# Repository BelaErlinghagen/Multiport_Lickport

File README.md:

# The Multiport Setup

**A behavioral setup for mice with 16 reward ports, multiple light/sound cues and real time pose estimation.**

<p align="center">
  <em>
    <b>Figure 1: The Multiport Setup.</b>
    <b>A)</b> Complete view of the Multiport Setup.
    <b>B)</b> Testing adjustments to the setup to show that the capacitive sensor of the Lick-O-Tron detects mouse licks.
    A Basler daA1440 was used to record the lickport. The mouse was given condensed milk (white droplet in C) manually through the shown tube.
    <b>C)</b> <i>Top:</i> Timeline over the entire session, with sensor activations marked as blue bars.
    <i>Bottom:</i> Zoom into one lick detection.
  </em>
</p>

---

## Table of Contents

- [Components of the Multiport Setup](#components-of-the-multiport-setup)
  - [Arena](#arena)
  - [Lick-O-Tron and PORTMASTER](#lick-o-tron-and-portmaster)
  - [Computer](#computer)
  - [Projector](#projector)
  - [Camera](#camera)
  - [Screens](#screens)
- [The Lick-O-Tron Lickport](#the-lick-o-tron-lickport)
  - [Design](#design)
  - [Assembly](#assembly)
    - [Parts](#parts)
    - [Step 1: Soldering](#step-1-soldering)
    - [Step 2: Uploading the code and testing the sensor](#step-2-uploading-the-code-and-testing-the-sensor)
    - [Step 3: Preparing the cannula](#step-3-preparing-the-cannula)
    - [Step 4: Assembly](#step-4-assembly)
    - [Step 5: Add the pump](#step-5-add-the-pump)
  - [Usage](#usage)
- [The PORTMASTER](#the-portmaster)
  - [Design](#design-1)
  - [Assembly](#assembly-1)
    - [Parts](#parts-1)
    - [Step 1: Solder pins and connector pieces to the PCB](#step-1-solder-pins-and-connector-pieces-to-the-pcb)
    - [Step 2: Wiring](#step-2-wiring)
  - [Usage](#usage-1)
- [Credit](#credit)

---

## Components of the Multiport Setup

### Arena

The arena is built from 16 [red acrylic wall panels](ArenaFiles/ArenaWall.stp), held together by 16 [connector pieces](ArenaFiles/AnglePiece.stp). This circular assembly stands on a sheet of acrylic that has been roughened on one side, which makes it more comfortable for the mice to walk on and prevents light projected onto the arena floor from being reflected.

In addition to the circular Multiport arena, two inlets were created to form a Y-Maze.

### Lick-O-Tron and PORTMASTER

The **Lick-O-Tron** is a self-built lickport module consisting of a capacitive sensor, an LED and a MOSFET relay to trigger a pump or valve.

The **PORTMASTER** is a hub that connects all Lick-O-Trons to the master Arduinos and delivers power to the pumps.

Both components are documented in detail below: see [The Lick-O-Tron Lickport](#the-lick-o-tron-lickport) and [The PORTMASTER](#the-portmaster).

### Computer

The computer used in this build was a Lenovo Thinkstation with the following specifications:

| Component | Specification |
| :--- | :--- |
| CPU | Intel(R) Core(TM) i7-14700K |
| GPU | Nvidia GeForce RTX 4060 |
| OS  | Ubuntu 24.04 |

To run live inference with DeepLabCut, CUDA was installed alongside the necessary Nvidia GPU drivers. Pixi was used to manage the Python environment of the software; the `.lock` and `.toml` files can be found in this repository.

### Projector

A BenQ Cinema Master Projector was mounted approximately 200 cm above the arena floor.

### Camera

A Basler daA3840-45uc camera with an Evetar lens (E3417A F2.4 f2.5mm 1/1.8") was mounted 40 cm below the arena floor.

### Screens

In the Y-Maze configuration, two Adafruit screens (5" 800x480 HDMI Backpack) were used to display patterns for the mice. The screens were mounted on [custom holders](ArenaFiles/YMaze_ScreenHolder.stp) that fit the Y-Maze configuration, and were connected directly to the computer via HDMI.

---

# Documentation for the Lick-O-Tron and the PORTMASTER

The Lick-O-Tron lickport and the PORTMASTER connectivity board are the two major components that act together in the automated Multiport system. Their design, assembly and usage are explained in detail below. The files needed to recreate the two modules can be found in their respective folders.

## The Lick-O-Tron Lickport

The idea behind the Lick-O-Tron was to create a lickport for behavioral mouse experiments that can:

1. Register lick events via a capacitive sensor.
2. Connect to up to two peristaltic pumps, which can independently eject precise volumes of liquid.
3. Allow flexible control of an LED located next to the needle.

### Design

The Lick-O-Tron contains three submodules: one Arduino proMicro and two MOSFET relay modules. The Arduino proMicro, as well as the power outlets of the MOSFET relay modules, receive power via the main connector (8-pin plug).

The Arduino's job is to register licks via a capacitive sensor — a cannula connected to the single pin at the bottom of the Lick-O-Tron. This is achieved with the code found [here](Lick-O-Tron/LickportArduinoCode.ino). The Arduino then transmits binary data about lick events to the Arduino Megas housed on the PORTMASTER.

The MOSFET modules are activated by the master Arduinos on the PORTMASTER and can trigger peristaltic pumps (or valves, etc.). The idea is that lick information is received by the master Arduinos, which then activate the pumps at set timepoints and with set PWM, depending on the needs of the experimenter. This allows for very flexible control of liquid dispensation. The Lick-O-Tron further connects the master Arduinos to an LED, which can be controlled independently.

<p align="center">
  <em><b>Figure 2:</b> 3D CAD model renderings for the Lick-O-Tron (left: front, middle: back, right: case). Note that the Pin Connectors are not depicted correctly in this Figure: The 8 Pin Header is straight and supposed to be soldered onto the other side of the PCB and the two angular 2 Pin Headers are also depicted on the wrong side of the PCB.</em>
</p>

### Assembly

#### Parts

| Item | Quantity | Manufactured by | EAN |
| :--- | ---: | :--- | ---: |
| Joy It proMicro | 1 | Joy It | 4250236822907 |
| MOSFET Relay Module | 2 | for example GERUI | 0744243396666 |
| Mini Peristaltic Pump | 1 (up to 2) | Whadda | 5410329730017 |
| Lick-O-Tron PCB | 1 | Eurocircuits | None: see folder in repo |
| Lick-O-Tron Case Parts | 1 each | 3D printed | None: see folder in repo |
| LED (white) | 1 | TRU Components | 2050004902785 |
| 10 MOhm Resistor (R1) | 1 | TRU Components | 2050004926057 |
| 470 Ohm Resistor (R2) | 1 | TRU Components | 4016139313023 |
| M3 Screws | 4 | Toolcraft | 4064161107578 |
| M3 Nuts | 4 | SWG Hox | 4053056028951 |
| Sterican Cannula | 2 | Roth | - |

#### Step 1: Soldering

With the PCB, the proMicro, the LED, the resistors, some pins and the relay modules at hand, the first step is to solder all of these components onto the PCB. By the end, the PCB should look similar to what is shown in Figure 2.

#### Step 2: Uploading the code and testing the sensor

Upload the Lick-O-Tron [code](Lick-O-Tron/LickportArduinoCode.ino) from this repository to the Joy It proMicro using the Arduino IDE. Then use the serial monitor to test whether touching the sensor pin registers something.

#### Step 3: Preparing the cannula

<p align="center">
  <em><b>Figure 3:</b> Example cannula assembly.</em>
</p>

To electrically connect the cannula to the sensor pin, a wire was wrapped around the cannula and clamped to it, and a second wire was then soldered onto the first one. This second wire was soldered to a pin connector piece, which connects to the sensor pin.

#### Step 4: Assembly

Once all these pieces are ready, the Lick-O-Tron can be assembled. In the Multiport build previewed here, the PCB was simply placed into the 3D-printed chamber and everything was screwed together directly onto the arena, where the spout frame had already been fixed into the acrylic sheets.

#### Step 5: Add the pump

To add the pump, solder two wires to the solder flags and their other ends to a pin connector. To rebuild the setup shown here exactly, 3D print the pump holder pieces and attach the pump as shown in Figure 4.

### Usage

<p align="center">
  <em><b>Figure 4:</b> All pieces together.</em>
</p>

The Lick-O-Tron is connected to the PORTMASTER via an 8-band ribbon cable. One PORTMASTER can control up to 16 Lick-O-Trons.

---

## The PORTMASTER

<p align="center">
  <em><b>Figure 5:</b> The PORTMASTER rack, lid opened.</em>
</p>

### Design

The PORTMASTER is designed to:

- power up to five 6 V pumps comfortably (more are possible);
- provide an easily accessible interface between the Arduinos and the computer, BNCs and power supply.

### Assembly

#### Parts

| Item | Quantity | Manufactured by | EAN |
| :--- | ---: | :--- | ---: |
| Arduino Mega 2560 Rev3 | 2 | Arduino | 7630049200067 |
| 8-band ribbon cable | - | - | - |
| 8-Way IDC Connector Female for Cable, 1 Row | 32 | Wurth Elektronik | 661008151923 (Mf. part #) |
| PORTMASTER PCB | 1 | Eurocircuits | None: see folder in repo |
| RSP-100-5 SMPSU 5V DC 20A 100W | 1 | MEAN WELL | 4711287435657 |

> **Note:** The remaining parts visible in Figure 5 have been left out on purpose, as they are specific to the space in which the Multiport Setup — and especially the PORTMASTER — was housed.

#### Step 1: Solder pins and connector pieces to the PCB

To connect the two Arduino Megas to the PCB, first solder the pins and the connector pieces for the power supply and the BNCs onto the PCB.

#### Step 2: Wiring

Once the Arduinos are in place, all that is left to do is the wiring. The 16 Lick-O-Trons are connected using an 8-band ribbon cable together with two 8-way IDC connectors, one going on the Lick-O-Tron and one on the PORTMASTER. Then the power supply needs to be connected to mains power and to the PCB. In the build showcased here, male BNC plugs were also connected to the PCB.

> **Safety:** Make sure to properly ground the casing of the PORTMASTER.

### Usage

The PORTMASTER can be connected to a computer via two USB-B to USB-A cables. It can then be used with the [custom software](Multiport_Code) in this repository.

---

## Credit

The Lick-O-Tron and the PORTMASTER were conceptualized and designed by Bela Erlinghagen, with extensive support from [Trace Robbins](https://github.com/R-Trace) and [Ben Escribano](https://github.com/BenjaminEscribano) of the iBehave CADRE ([website](https://ibehave.nrw/ibots-platform/cadre/), [GitHub](https://github.com/iBehave-CADRE)).

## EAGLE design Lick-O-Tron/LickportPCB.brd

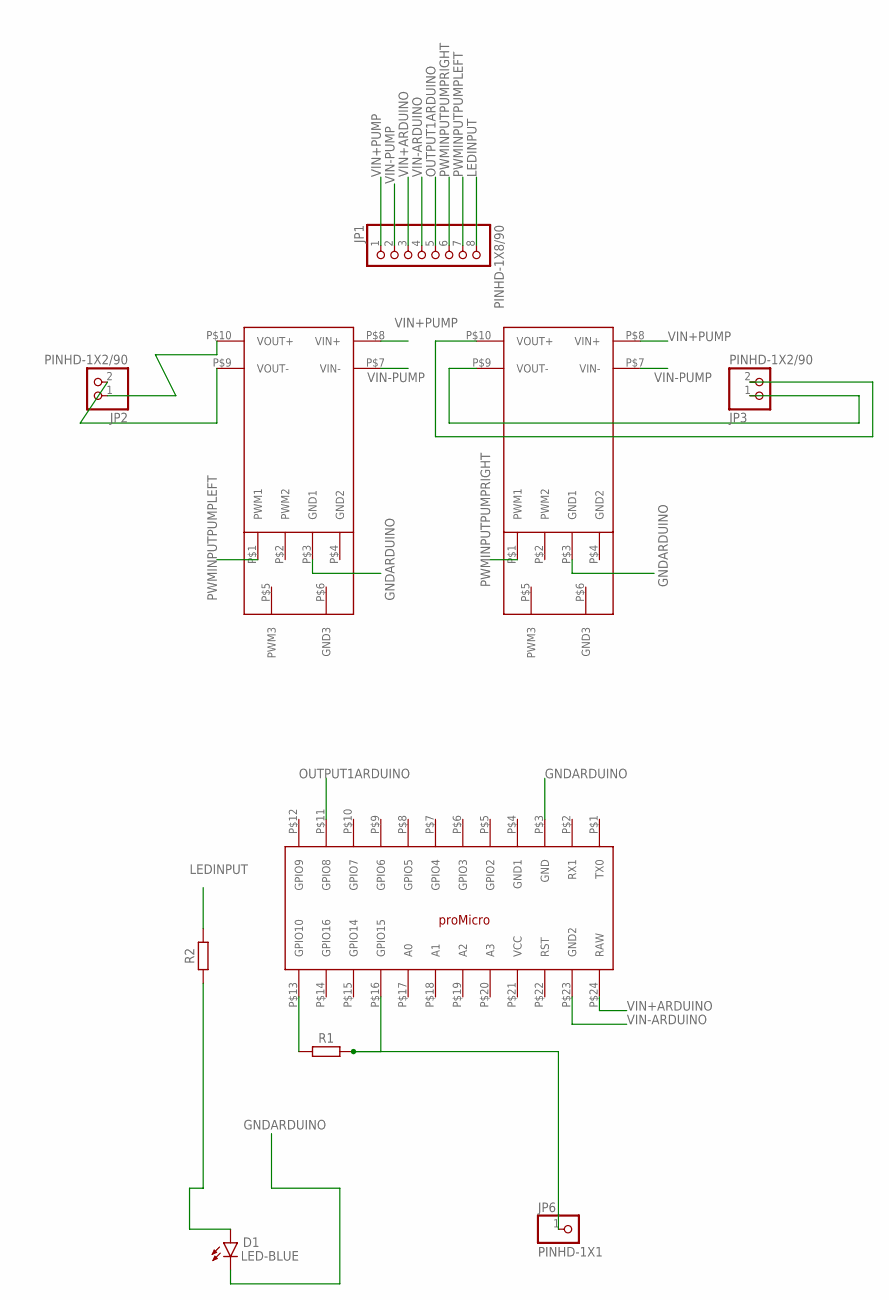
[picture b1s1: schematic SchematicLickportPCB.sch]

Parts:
D1: LED-BLUE; LEDRD254W60D565H860B_B
JP1: PINHD-1X8/90; 1X08/90
JP2, JP3: PINHD-1X2/90; 1X02/90
JP6: PINHD-1X1; 1X01
R1, R2: RESISTOR_AXIAL-11.7MM-PITCH; RESAD1176W63L850D250B
U$1, U$2: MOSFET_MODULE
U$3: JOY_IT_PRO_MICRO

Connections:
GNDARDUINO: D1.C, U$1.P$3 (GND1), U$2.P$3 (GND1), U$3.P$3 (GND)
LEDINPUT: JP1.8, R2.2
unnamed: JP2.1, U$1.P$10 (VOUT+)
unnamed: JP2.2, U$1.P$9 (VOUT-)
unnamed: JP3.2, U$2.P$10 (VOUT+)
unnamed: JP3.1, U$2.P$9 (VOUT-)
unnamed: D1.A, R2.1
unnamed: R1.1, U$3.P$13 (GPIO10)
unnamed: JP6.1, R1.2, U$3.P$16 (GPIO15)
OUTPUT1ARDUINO: JP1.5, U$3.P$11 (GPIO8)
PWMINPUTPUMPLEFT: JP1.7, U$1.P$1 (PWM1)
PWMINPUTPUMPRIGHT: JP1.6, U$2.P$1 (PWM1)
VIN+ARDUINO: JP1.3, U$3.P$24 (RAW)
VIN+PUMP: JP1.1, U$1.P$8 (VIN+), U$2.P$8 (VIN+)
VIN-ARDUINO: JP1.4, U$3.P$23 (GND2)
VIN-PUMP: JP1.2, U$1.P$7 (VIN-), U$2.P$7 (VIN-)

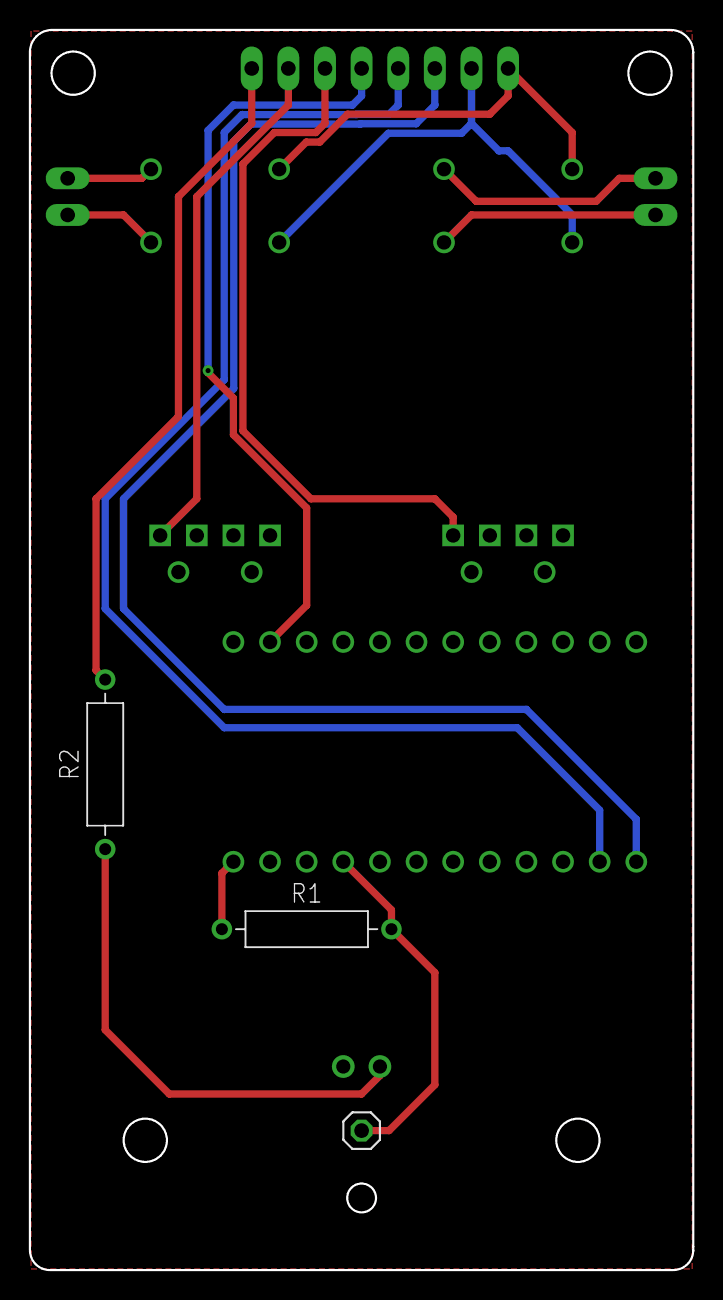
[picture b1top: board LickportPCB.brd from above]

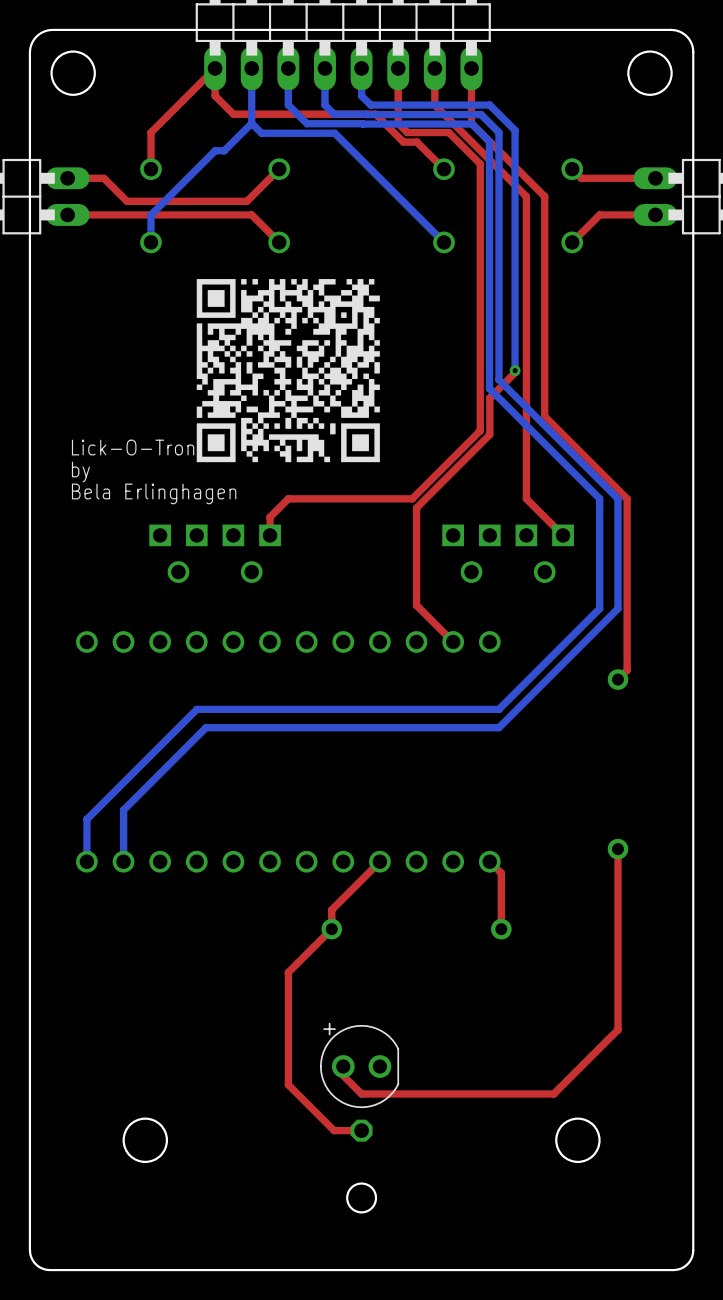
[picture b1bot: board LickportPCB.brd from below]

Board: 2 copper layers, 46.0 x 86.0 mm, 10 parts (4 on the bottom side), 16 nets.

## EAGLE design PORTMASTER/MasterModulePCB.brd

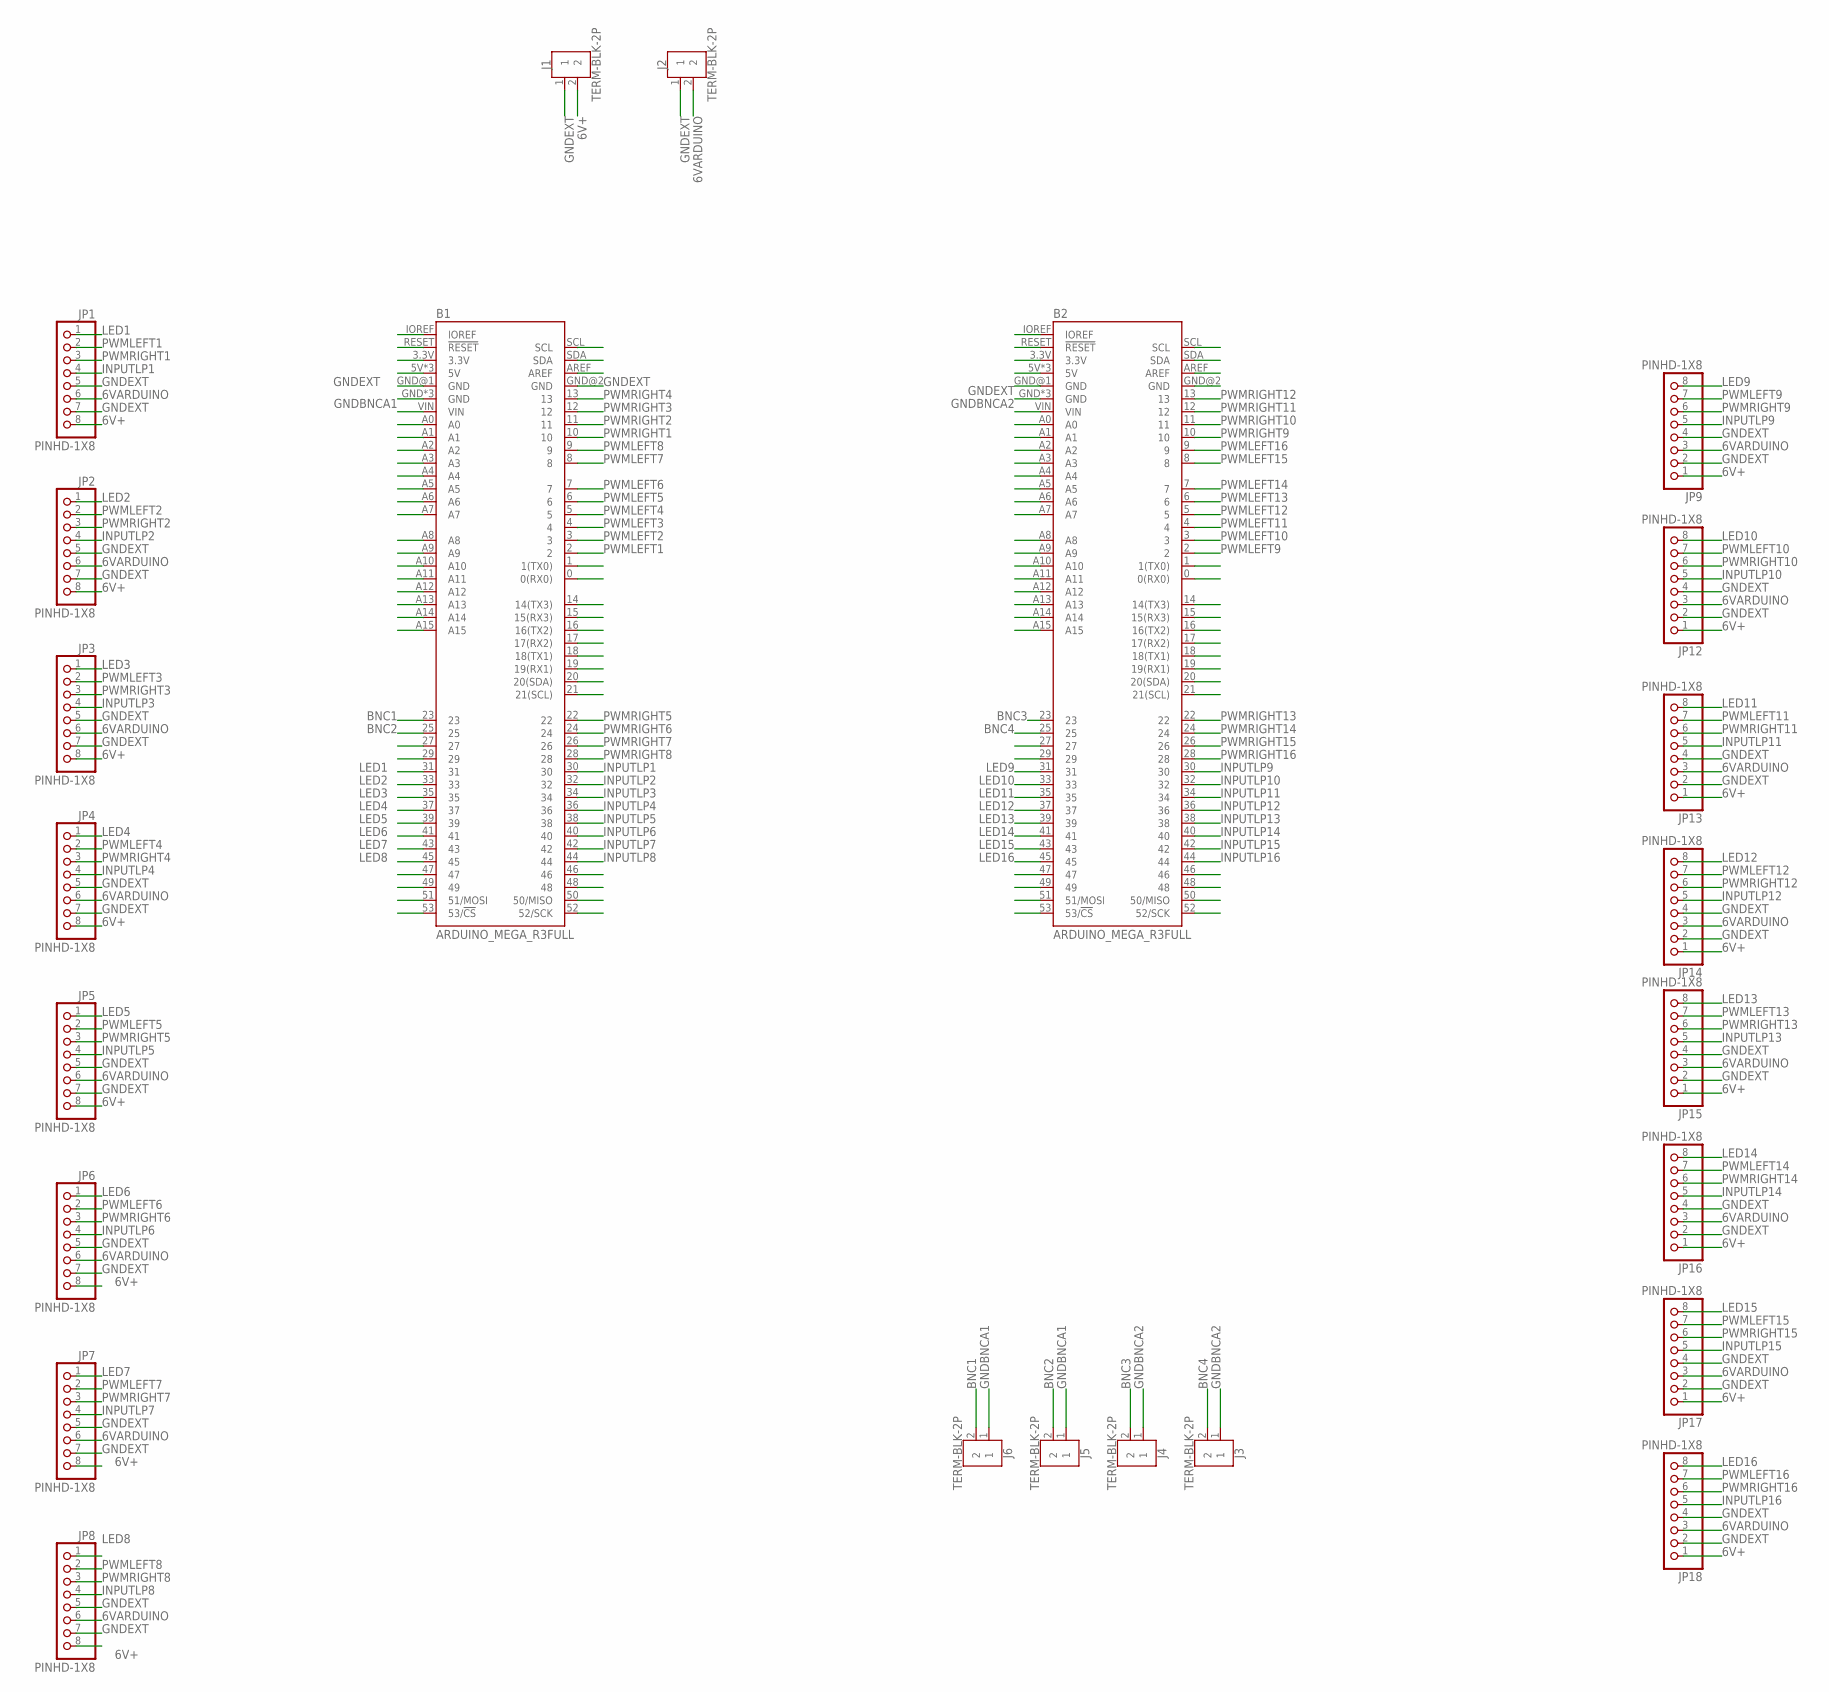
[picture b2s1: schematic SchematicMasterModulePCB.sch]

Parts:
B1, B2: ARDUINO_MEGA_R3FULL; ARDUINO_MEGA_NO_SILK
J1, J2, J3, J4, J5, J6: TERM-BLK-2P; TERMBLK_508-2N
JP1, JP2, JP3, JP4, JP5, JP6, JP7, JP8, JP9, JP12, JP13, JP14, JP15, JP16, JP17, JP18: PINHD-1X8; 1X08

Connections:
6V+: J1.2, JP1.8, JP2.8, JP3.8, JP4.8, JP5.8, JP6.8, JP7.8, JP8.8, JP9.1, JP12.1, JP13.1, JP14.1, JP15.1, JP16.1, JP17.1, JP18.1
6VARDUINO: J2.2, JP1.6, JP2.6, JP3.6, JP4.6, JP5.6, JP6.6, JP7.6, JP8.6, JP9.3, JP12.3, JP13.3, JP14.3, JP15.3, JP16.3, JP17.3, JP18.3
BNC1: B1.23, J6.2
BNC2: B1.25, J5.2
BNC3: B2.23, J4.2
BNC4: B2.25, J3.2
GNDBNCA1: B1.GND, B1.GND@3 (GND), B1.GND@4 (GND), J5.1, J6.1
GNDBNCA2: B2.GND, B2.GND@3 (GND), B2.GND@4 (GND), J3.1, J4.1
GNDEXT: B1.GND@1 (GND), B1.GND@2 (GND), B2.GND@1 (GND), J1.1, J2.1, JP1.5, JP1.7, JP2.5, JP2.7, JP3.5, JP3.7, JP4.5, JP4.7, JP5.5, JP5.7, JP6.5, JP6.7, JP7.5, JP7.7, JP8.5, JP8.7, JP9.2, JP9.4, JP12.2, JP12.4, JP13.2, JP13.4, JP14.2, JP14.4, JP15.2, JP15.4, JP16.2, JP16.4, JP17.2, JP17.4, JP18.2, JP18.4
INPUTLP1: B1.30, JP1.4
INPUTLP2: B1.32, JP2.4
INPUTLP3: B1.34, JP3.4
INPUTLP4: B1.36, JP4.4
INPUTLP5: B1.38, JP5.4
INPUTLP6: B1.40, JP6.4
INPUTLP7: B1.42, JP7.4
INPUTLP8: B1.44, JP8.4
INPUTLP9: B2.30, JP9.5
INPUTLP10: B2.32, JP12.5
INPUTLP11: B2.34, JP13.5
INPUTLP12: B2.36, JP14.5
INPUTLP13: B2.38, JP15.5
INPUTLP14: B2.40, JP16.5
INPUTLP15: B2.42, JP17.5
INPUTLP16: B2.44, JP18.5
LED1: B1.31, JP1.1
LED2: B1.33, JP2.1
LED3: B1.35, JP3.1
LED4: B1.37, JP4.1
LED5: B1.39, JP5.1
LED6: B1.41, JP6.1
LED7: B1.43, JP7.1
LED8: B1.45, JP8.1
LED9: B2.31, JP9.8
LED10: B2.33, JP12.8
LED11: B2.35, JP13.8
LED12: B2.37, JP14.8
LED13: B2.39, JP15.8
LED14: B2.41, JP16.8
LED15: B2.43, JP17.8
LED16: B2.45, JP18.8
unnamed: B2.5V, B2.5V@1 (5V), B2.5V@2 (5V)
unnamed: B1.5V, B1.5V@1 (5V), B1.5V@2 (5V)
PWMLEFT1: B1.2, JP1.2
PWMLEFT2: B1.3, JP2.2
PWMLEFT3: B1.4, JP3.2
PWMLEFT4: B1.5, JP4.2
PWMLEFT5: B1.6, JP5.2
PWMLEFT6: B1.7, JP6.2
PWMLEFT7: B1.8, JP7.2
PWMLEFT8: B1.9, JP8.2
PWMLEFT9: B2.2, JP9.7
PWMLEFT10: B2.3, JP12.7
PWMLEFT11: B2.4, JP13.7
PWMLEFT12: B2.5, JP14.7
PWMLEFT13: B2.6, JP15.7
PWMLEFT14: B2.7, JP16.7
PWMLEFT15: B2.8, JP17.7
PWMLEFT16: B2.9, JP18.7
PWMRIGHT1: B1.10, JP1.3
PWMRIGHT2: B1.11, JP2.3
PWMRIGHT3: B1.12, JP3.3
PWMRIGHT4: B1.13, JP4.3
PWMRIGHT5: B1.22, JP5.3
PWMRIGHT6: B1.24, JP6.3
PWMRIGHT7: B1.26, JP7.3
PWMRIGHT8: B1.28, JP8.3
PWMRIGHT9: B2.10, JP9.6
PWMRIGHT10: B2.11, JP12.6
PWMRIGHT11: B2.12, JP13.6
PWMRIGHT12: B2.13, JP14.6
PWMRIGHT13: B2.22, JP15.6
PWMRIGHT14: B2.24, JP16.6
PWMRIGHT15: B2.26, JP17.6
PWMRIGHT16: B2.28, JP18.6

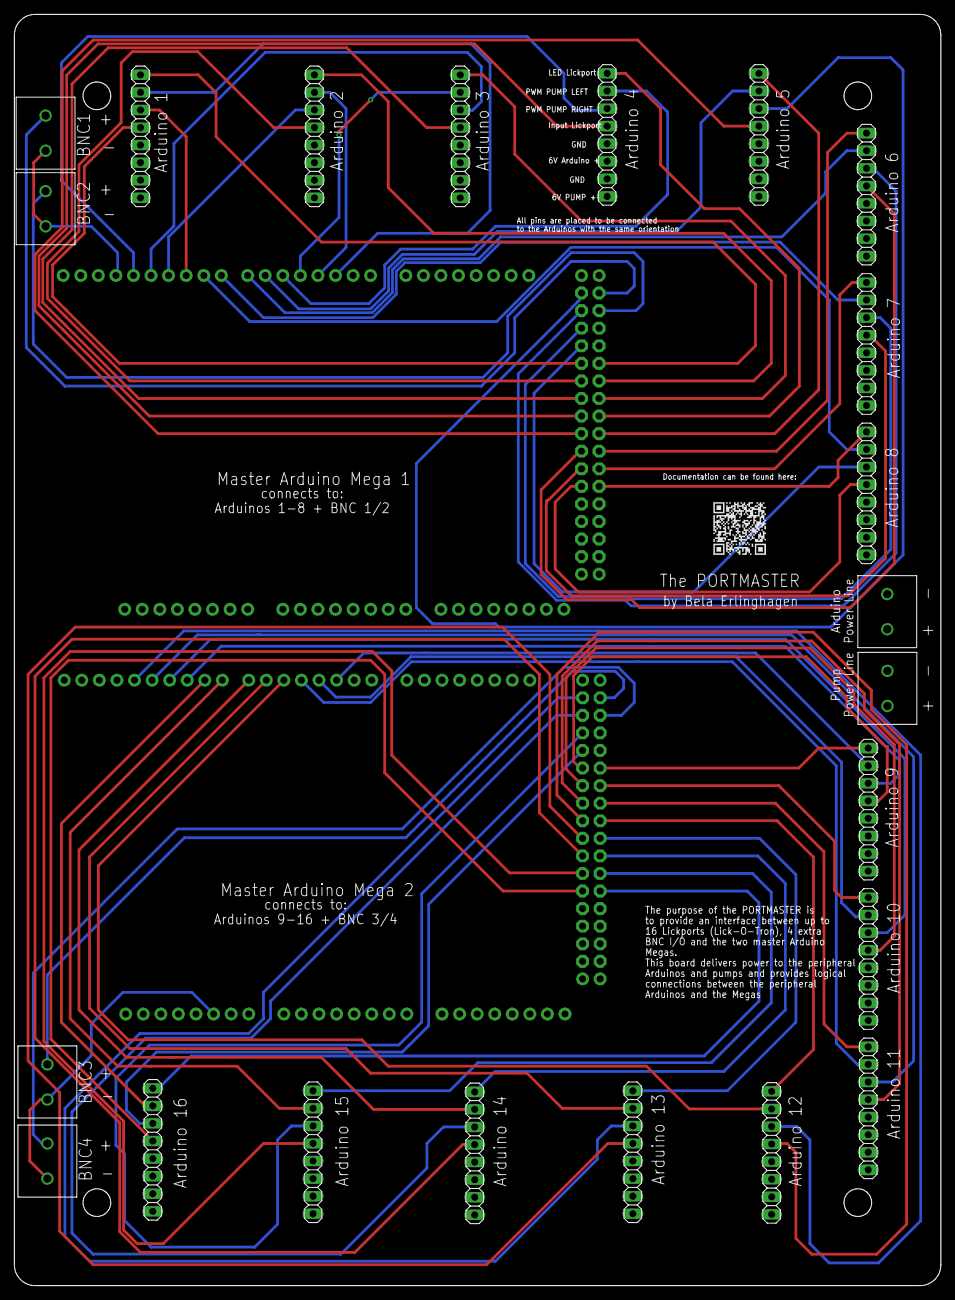
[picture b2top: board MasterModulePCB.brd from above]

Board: 4 copper layers, 133.9 x 183.8 mm, 24 parts (0 on the bottom side), 75 nets.

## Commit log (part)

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2025-09-22 Rename LickportPCB v33_2025-09-22.zip to GerberFiles_LickportPCB_v33_2025-09-22.zip
2025-09-22 Rename JOY_IT_PRO_MICRO.stl to JOY_IT_PRO_MICRO(fromGrabCADbyAndrew_Whitham).stl
2026-03-26 Added Code Folder
2026-03-26 Restructuring Portmaster Folder
2026-03-27 Update PortMasterArduinoCode.ino
    Edited PortMasterArduinoCode
2026-03-27 Serial Controls begun
2026-03-27 serial communication established
2026-03-27 Adjusted PortmasterCode
2026-03-27 Finished serial read functionality
2026-03-27 Serial lookup tables established
2026-03-27 started working on serial communication
2026-03-30 turned serial commands into class
2026-03-30 Started getting into writing functionality
2026-03-31 implemented reading and writing functionality in serial controls class
2026-03-31 added pypylon and started to add deeplabcutlive+pytorch
2026-03-31 started working on camera controls
2026-04-01 fixed deeplabcut and pytorch installation.
2026-04-01 started implementing camera functionality
2026-04-01 Fixed camera_on
2026-04-01 Test
2026-04-02 started working on multiprocessing and gui functionality but not working yet.
2026-04-03 Implemented Plotting functionality with Qt
2026-04-03 Redesigned GUI and plotting functionality
2026-04-06 Introduced downsampling and reshaping functionality
2026-04-07 Camera live replay is working now
2026-04-08 Started implementing saving functionality
2026-04-08 Saving Start/stop implemented
2026-04-09 Folder Creation + Actual Data Saving implemented
2026-04-10 Added left panel to the gui
2026-04-15 Added Cleaning and Testing functionality, worked on removing the flickering
2026-04-16 Implemented Experiment page of GUI
2026-04-16 Started working on the protocol functionality
2026-04-17 Fixed some bugs in protocl functionality and added mouse_file functionality.
2026-04-23 started establishing deeplabcut and iti functionality
